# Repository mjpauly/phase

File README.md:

# Phase Keyboard

- Kyria stagger, Corne thumb cluster, Ferris-inspired electronics.
- USB-C
- Reversible PCB for use with both hands.
- MX-style key switch support with optional Kailh hot swap sockets.
- 42 keys.

A one-off moon-themed sand-cast aluminum case was also designed in Spring 2022. See [here](https://imgur.com/a/QfmxirT) for photos of the manufacturing process!

## Versions

### Version 1.0.1

- Assembled and tested
- Fixes SDA/SCL swap
- Removes silkscreen art (just too cluttered)
- Gerbers are at `phase/JLCPCB_2022-01-29_v1_0_1.zip`.

### Version 1.0.0

- Manufactured with JLCPCB, built, and tested.
- SDA and SCL are swapped, so some rework is required. The traces need to be cut, soldermask has to be scraped away, and wires have to be soldered where the soldermask was removed. See the image at `img/phase_v1_0_0_rework.jpeg`. This is fixed in v1.0.1.
- Gerbers at `phase/JCLPCB_2020-09-21_v1_0_0.zip`.

## Firmware

Firmware can be found here: [https://github.com/mjpauly/qmk_firmware/tree/master/keyboards/phase](https://github.com/mjpauly/qmk_firmware/tree/master/keyboards/phase). It's not merged into mainline QMK, but if you want to use the design then I can make that happen.

## BOM

The BOM for SMD components can be found at `phase/bom-with-pns-lcsc.csv`. This lists the part numbers that can be purchased from [LCSC](https://lcsc.com). In addition to this, the following may also needed for a complete keyboard:
- TRRS connectors from [AliExpress](https://www.aliexpress.com/item/33029465106.html).
- A TRRS cable. [This one](https://www.amazon.com/gp/product/B019EHMN68?psc=1) is good.
- [Kailh hot swap sockets](https://kbdfans.com/products/mechanical-keyboard-switches-kailh-pcb-socket).
- MX style switches.
- Keycaps: 42x 1u, option for 2x 1.5u keycaps for the center-most thumb keys.
- USB-C cable.
- Rubber feet. [3M SJ5376](https://www.digikey.com/en/products/detail/3m/SJ5376/3866077) are tall enough to work with the hot swap sockets and narrow enough to fit in the pattern of keys.

## Part libraries

All non-standard parts are in the project library except for the keyswitch footprint `Kailh_socket_MX_optional_reversible` from [daprice](https://github.com/daprice/keyswitches.pretty). Credit also goes to [Keebio](https://github.com/keebio/Keebio-Parts.pretty) for the TRRS connector footprint `TRRS-PJ-320A-dual`.

## Silkscreen on v1.0.0

The silkscreen is based on the following images generated with Processing. I felt like this made the PCB too cluttered, so it's removed in the latest version.

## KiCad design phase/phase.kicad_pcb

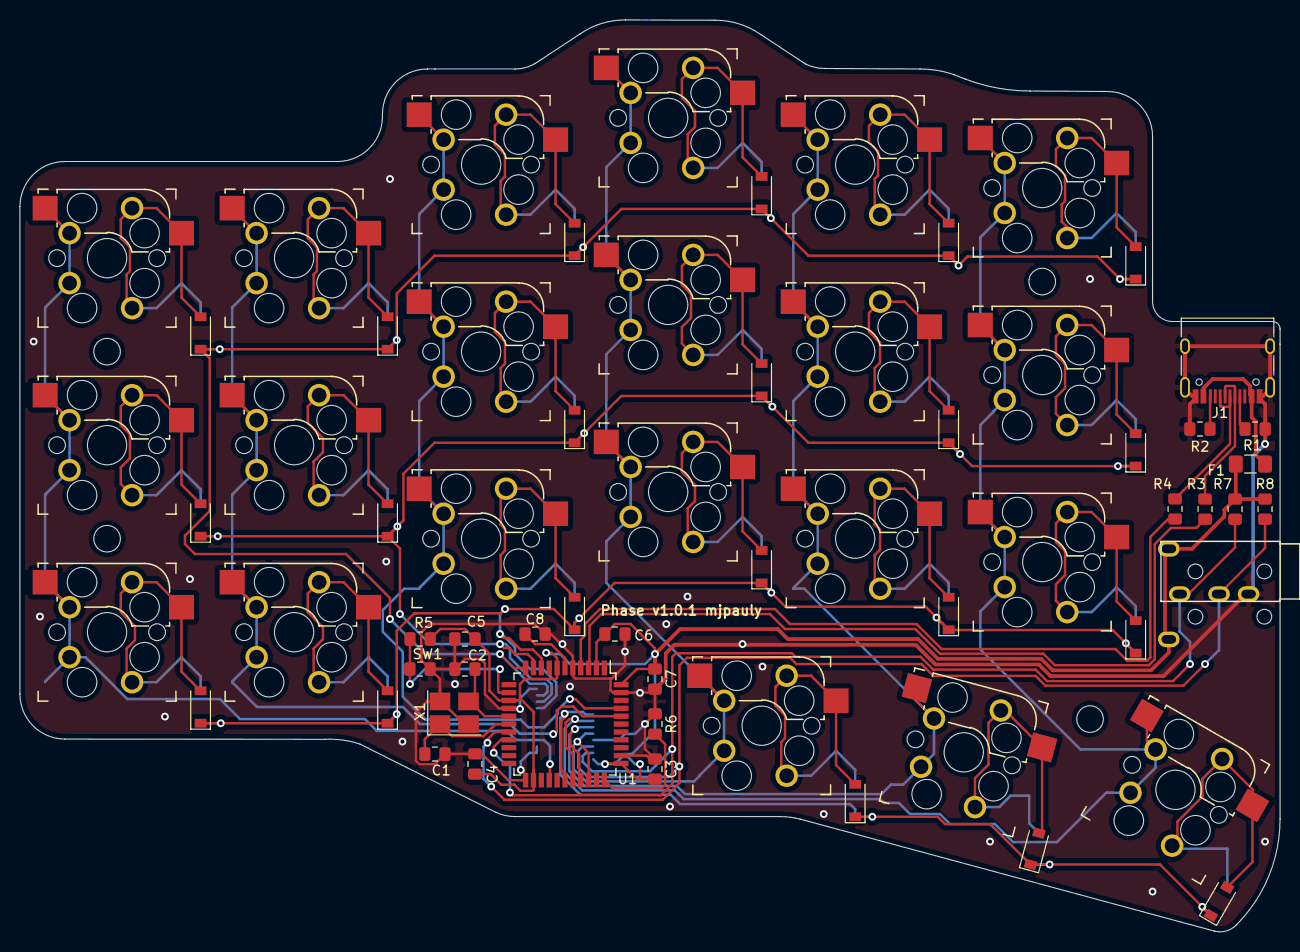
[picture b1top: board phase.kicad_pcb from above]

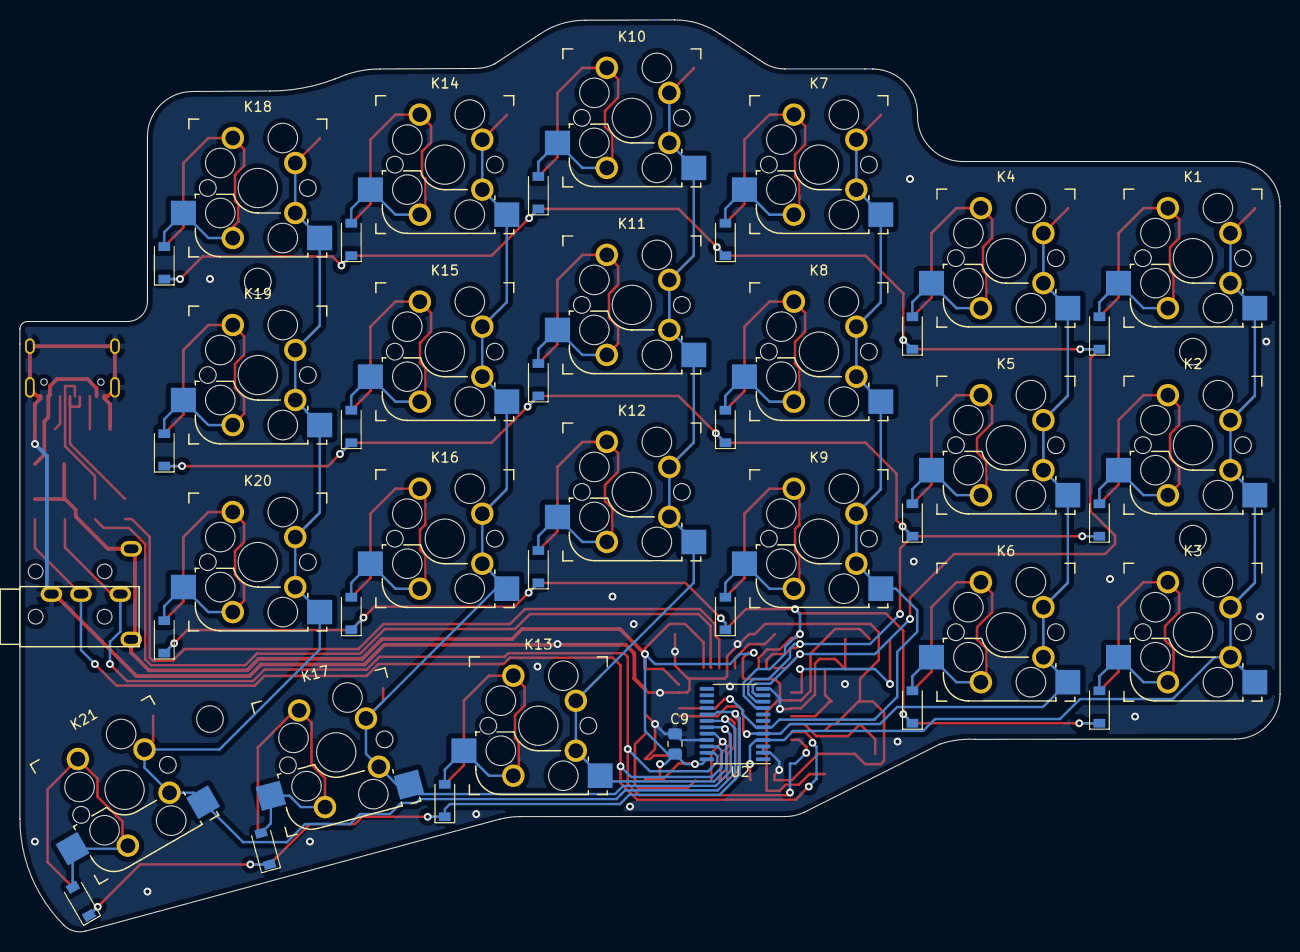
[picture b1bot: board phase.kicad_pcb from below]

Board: 2 copper layers, 128.0 x 92.6 mm, 66 parts (2 on the bottom side), 47 nets.

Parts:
C1, C2: 22p; C_0805_2012Metric_Pad1.15x1.40mm_HandSolder
C3, C4, C5, C6, C9: 0.1u; C_0805_2012Metric_Pad1.15x1.40mm_HandSolder
C7: 4.7u; C_0805_2012Metric_Pad1.15x1.40mm_HandSolder
C8: 1u; C_0805_2012Metric_Pad1.15x1.40mm_HandSolder
D1, D2, D3, D4, D5, D6, D7, D8, D9, D10, D11, D12, D13, D14, D15, D16, D17, D18, D19, D20, D21: D; D_SOD-123-dual
F1: 500mA; Fuse_1206_3216Metric_Pad1.42x1.75mm_HandSolder
J1: USB_C_Receptacle_USB2.0; USB_C_Receptacle_HRO_TYPE-C-31-M-12
J2: AudioJack4; TRRS-PJ-320A-dual
K1, K2, K3, K4, K5, K6, K7, K8, K9, K10, K11, K12, K13, K14, K15, K16, K17, K18, K19, K20, K21: KEYSW; Kailh_socket_MX_optional_reversible
R1, R2: 5.1k; R_0805_2012Metric_Pad1.15x1.40mm_HandSolder
R3, R4: 22; R_0805_2012Metric_Pad1.15x1.40mm_HandSolder
R5, R6: 10k; R_0805_2012Metric_Pad1.15x1.40mm_HandSolder
R7, R8: 4.7k; R_0805_2012Metric_Pad1.15x1.40mm_HandSolder
SW1: SW_Push; R_0805_2012Metric_Pad1.15x1.40mm_HandSolder
U1: ATmega32U4-AU; TQFP-44_10x10mm_P0.8mm
U2: PCA9555PW; TSSOP-24_4.4x7.8mm_P0.65mm
X1: Crystal_GND24_Small; Crystal_SMD_3225-4Pin_3.2x2.5mm_HandSoldering

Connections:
+5V: C3.2, C4.2, C5.2, C6.2, C7.2, C9.2, F1.1, J2.T, R5.2, R7.2, R8.2, U1.2, U1.7, U1.14, U1.24, U1.34, U1.44, U2.24
/D+: R4.1, U1.4
/D-: R3.1, U1.3
/SCL: J2.R2, R8.1, U1.18, U2.22
/SDA: J2.R1, R7.1, U1.19, U2.23
/col0: K1.1, K2.1, K3.1, U1.26, U2.4
/col1: K4.1, K5.1, K6.1, U1.40, U2.5
/col2: K7.1, K8.1, K9.1, U1.41, U2.6
/col3: K10.1, K11.1, K12.1, K13.1, U1.31, U2.20
/col4: K14.1, K15.1, K16.1, K17.1, U1.30, U2.19
/col5: K18.1, K19.1, K20.1, K21.1, U1.29, U2.18
/row0: D1.1, D4.1, D7.1, D10.1, D14.1, D18.1, U1.11, U2.11
/row1: D2.1, D5.1, D8.1, D11.1, D15.1, D19.1, U1.10, U2.10
/row2: D3.1, D6.1, D9.1, D12.1, D16.1, D20.1, U1.9, U2.9
/row3: D13.1, D17.1, D21.1, U1.28, U2.17
GND: C1.2, C2.2, C3.1, C4.1, C5.1, C6.1, C7.1, C8.1, C9.1, J1.A1, J1.A12, J1.B1, J1.B12, J1.S1, J2.S, R1.1, R2.1, R6.1, SW1.1, U1.5, U1.15, U1.23, U1.35, U1.43, U2.2, U2.3, U2.12, U2.21, X1.2, X1.4
unnamed: C1.1, U1.17, X1.1
unnamed: C2.1, U1.16, X1.3
unnamed: C8.2, U1.6
unnamed: D1.2, K1.2
unnamed: D2.2, K2.2
unnamed: D3.2, K3.2
unnamed: D4.2, K4.2
unnamed: D5.2, K5.2
unnamed: D6.2, K6.2
unnamed: D7.2, K7.2
unnamed: D8.2, K8.2
unnamed: D9.2, K9.2
unnamed: D10.2, K10.2
unnamed: D11.2, K11.2
unnamed: D12.2, K12.2
unnamed: D13.2, K13.2
unnamed: D14.2, K14.2
unnamed: D15.2, K15.2
unnamed: D16.2, K16.2
unnamed: D17.2, K17.2
unnamed: D18.2, K18.2
unnamed: D19.2, K19.2
unnamed: D20.2, K20.2
unnamed: D21.2, K21.2
unnamed: F1.2, J1.A4, J1.A9, J1.B4, J1.B9
unnamed: J1.A5, R1.2
unnamed: J1.A6, J1.B6, R4.2
unnamed: J1.A7, J1.B7, R3.2
unnamed: J1.B5, R2.2
unnamed: R5.1, SW1.2, U1.13
unnamed: R6.2, U1.33

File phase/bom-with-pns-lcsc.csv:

Item,Qty,Reference(s),Value,LibPart,Footprint,Datasheet,LCSC PN
1,2,"C1, C2",22p,Device:C_Small,Capacitor_SMD:C_0805_2012Metric_Pad1.15x1.40mm_HandSolder,~,C1804
2,5,"C3, C4, C5, C6, C9",0.1u,Device:C_Small,Capacitor_SMD:C_0805_2012Metric_Pad1.15x1.40mm_HandSolder,~,C49678
3,1,C7,4.7u,Device:C_Small,Capacitor_SMD:C_0805_2012Metric_Pad1.15x1.40mm_HandSolder,~,C1779
4,1,C8,1u,Device:C_Small,Capacitor_SMD:C_0805_2012Metric_Pad1.15x1.40mm_HandSolder,~,C28323
5,42,"D1, D2, D3, D4, D5, D6, D7, D8, D9, D10, D11, D12, D13, D14, D15, D16, D17, D18, D19, D20, D21",D,Device:D,phase:D_SOD-123-dual,~,C81598
6,1,F1,500mA,Device:Polyfuse,Fuse:Fuse_1206_3216Metric_Pad1.42x1.75mm_HandSolder,~,C151162
7,1,J1,USB_C_Receptacle_USB2.0,Connector:USB_C_Receptacle_USB2.0,Connector_USB:USB_C_Receptacle_HRO_TYPE-C-31-M-12,https://www.usb.org/sites/default/files/documents/usb_type-c.zip,C165948
8,2,J2,AudioJack4,Connector:AudioJack4,phase:TRRS-PJ-320A-dual,~,
9,42,"K1, K2, K3, K4, K5, K6, K7, K8, K9, K10, K11, K12, K13, K14, K15, K16, K17, K18, K19, K20, K21",KEYSW,keyboard_parts:KEYSW,keyswitches:Kailh_socket_MX_optional_reversible,,
10,2,"R1, R2",5.1k,Device:R_Small_US,Resistor_SMD:R_0805_2012Metric_Pad1.15x1.40mm_HandSolder,~,C27834
11,2,"R3, R4",22,Device:R_Small_US,Resistor_SMD:R_0805_2012Metric_Pad1.15x1.40mm_HandSolder,~,C17561
12,2,"R5, R6",10k,Device:R_Small_US,Resistor_SMD:R_0805_2012Metric_Pad1.15x1.40mm_HandSolder,~,C17414
13,2,"R7, R8",4.7k,Device:R_Small_US,Resistor_SMD:R_0805_2012Metric_Pad1.15x1.40mm_HandSolder,~,C17673
15,1,U1,ATmega32U4-AU,MCU_Microchip_ATmega:ATmega32U4-AU,Package_QFP:TQFP-44_10x10mm_P0.8mm,http://ww1.microchip.com/downloads/en/DeviceDoc/Atmel-7766-8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,C44854
16,1,U2,PCA9555PW,Interface_Expansion:PCA9555PW,Package_SO:TSSOP-24_4.4x7.8mm_P0.65mm,https://www.nxp.com/docs/en/data-sheet/PCA9555.pdf,C128392
17,1,X1,Crystal_GND24_Small,Device:Crystal_GND24_Small,Crystal:Crystal_SMD_3225-4Pin_3.2x2.5mm_HandSoldering,~,C13738

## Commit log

2021-05-14 add phase v1 files
2021-05-14 update note about part libraries
2022-01-29 renamed files to remove version number, add gitignore
2022-01-30 more renaming
2022-01-30 fix sda/scl swap, remove silkscreen art and unneeded ref des
2022-04-13 add 3d model
2022-06-09 update with v1.0.1 results, add info about one-off aluminum case project
